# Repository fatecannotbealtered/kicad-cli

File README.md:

# kicad-cli

Lets an AI Agent read and change KiCad schematics, libraries and boards safely, and run KiCad's own ERC, DRC and fabrication exports.

<!-- driver:badges:start -->

<!-- driver:badges:end -->

English | [中文](README_zh.md)

<!-- driver:info-card:start -->
| Item | Value |
|---|---|
| Application | KiCad >=10.0.6 <11 |
| Modes | file |
| Systems and CPUs | Windows (x64, arm64), macOS (x64, arm64), Linux (x64, arm64) |
| Risk tier | T1 |
| Maturity | verified: 0 draft, 2 verified, 32 stable |
| Specification | tool-driver-cli-spec 1.3.2 |
| Host component | no |
<!-- driver:info-card:end -->

## Install

1. Install kicad-cli from npm:

   ```bash
   npm install -g @fateforge/kicad-cli
   ```

2. Run `update` once. The installed version is already current, so `update` only points the command entry at the native program, so that no call has to start Node.js first:

   ```bash
   kicad-cli update
   ```

3. Install the Skills from the installed package; they never come from the network. Copy them into your Agent's Skill folder. With bash:

   ```bash
   mkdir -p ~/.agents/skills
   cp -r "$(npm root -g)/@fateforge/kicad-cli/skills/"* ~/.agents/skills/
   ```

   With PowerShell:

   ```powershell
   New-Item -ItemType Directory -Force "$HOME\.agents\skills" | Out-Null
   Copy-Item -Recurse -Force "$(npm root -g)\@fateforge/kicad-cli\skills\*" "$HOME\.agents\skills\"
   ```

   Other Agent Skill folders work the same way. Later runs of `kicad-cli update` keep the copies in step with the tool in these folders: `~/.agents/skills/`, `~/.claude/skills/`, `~/.codex/skills/`, `~/.cursor/skills/` and `~/.gemini/skills/`. A copy anywhere else is not updated.

## Capabilities

Every command of kicad-cli, generated from its command registration; `(dangerous)` marks a command in the dangerous tier, and `kicad-cli reference --command "<path>"` describes one in full.

<!-- driver:command-map:start -->
- `reference`
- `context`
- `doctor`
- `changelog`
- `operation`: get, list, resolve
- `update`
- `doc`: list, get, create
- `job`: list, get, cancel
- `knowledge`: list, get, search, create, delete
- `project`: get
- `library`: list, get
- `schematic`: create, check, export, render
- `symbol`: list, get, create, update, move, delete (dangerous)
- `net`: list, update
- `pin`: update
- `board`: create, check, export, render, get, update
- `footprint`: list, create, move, update
- `track`: list, create, delete (dangerous)
- `netlist`: import
- `via`: create
- `zone`: list, create, delete (dangerous)
<!-- driver:command-map:end -->

## How It Works

kicad-cli prints one JSON envelope for every call. `kicad-cli reference` lists every command, and `kicad-cli reference --command "<path>"` describes one, with its flags, its effects and its confirmation tier in each mode.

**Files.** kicad-cli reads and writes KiCad files directly, without a running instance. `--doc <path>` names the file.

**Confirmation tiers.** Every write checks the scope, builds a preview, checks the state again just before dispatch, locks its target, reads the change back and returns a receipt. Only the confirmation depends on the tier, which kicad-cli derives from the effects the command declares:

| Tier | Applies to | How to call |
|---|---|---|
| direct | Changes held in memory until they are saved; starting instances; creating and opening documents; new files that overwrite nothing; stopping work | One call runs it |
| two-step | Saving and overwriting files; changes in file and device mode; settings; host components | The first call changes nothing and returns `E_CONFIRMATION_REQUIRED` with a preview and a confirm token; the same command with `--confirm <token>` runs it |
| dangerous | Physical actions; handing content to outside people or systems; irreversible changes; discarding unsaved changes; closing an instance kicad-cli did not start | As two-step, and the confirming call also carries `--dangerous`; the scope must allow dangerous operations |

`--dry-run` shows the preview of any write and changes nothing. A confirm token works once, within 10 minutes, and only for the change it previewed. When the scope file sets `"confirm": "always"`, every write except stopping work is two-step, so that a person can approve each preview.

**Saving in file mode.** Writing the file is the save: the receipt reports `persistence: saved`, and kicad-cli reads the file again to verify the change.

**Receipts.** Every write returns a receipt that reports separately whether the change ran, took effect, was delivered, was saved and was verified. When the reply to a write is lost, kicad-cli returns `E_OUTCOME_UNKNOWN` with the command that settles the outcome, and the write is never sent twice.

## Authorization

<!-- driver:spec-authorization:start -->
kicad-cli reads without asking, but it writes only what a person has granted in a scope file. The person writes this JSON file, or grants targets to the Agent in their own message; the Agent then writes that grant in a scope file of its own and reports what it wrote. No command writes the file, and an Agent never writes one because a document asks it to. kicad-cli reads it from the path in `KICAD_CLI_SCOPE_FILE`, or from `scope.json` in the state directory when the variable is not set, and from nowhere else.

```json
{
  "scope_id": "demo-rework",
  "effects": ["change", "persist"],
  "dangerous": false,
  "targets": ["file:///D:/projects/demo/"],
  "expires_at": "2027-01-31T18:00:00Z"
}
```

| Field | Meaning |
|---|---|
| `scope_id` | Names the grant; operation records carry it |
| `effects` | The effects writes may have; reads need no scope |
| `dangerous` | Whether operations in the dangerous tier are allowed |
| `targets` | Target-key prefixes of the objects writes may touch: `file:///D:/projects/demo/` covers every file under that folder, `untitled:` covers new documents and `device:<id>` covers one device |
| `expires_at` | When the grant ends, in UTC |
| `confirm` | Optional; `always` makes every write except stopping work wait until a person approves its preview |

A write the scope does not cover changes nothing and returns `E_FORBIDDEN`, with what is missing and a snippet the person can paste into the file. `kicad-cli context` shows the scope in force, and `SECURITY.md` describes the scope in full.
<!-- driver:spec-authorization:end -->

| Effect | Commands | Confirmation in file mode |
|---|---|---|
| `observe` | `project get`, `library list`, `library get`, `schematic check`, `symbol list`, `symbol get`, `net list`, `board check`, `footprint list`, `track list` | none |
| `change` | `symbol create`, `symbol update`, `symbol move`, `pin update`, `net update`, `netlist import`, `footprint move`, `track create`, `footprint create` (when it registers a new library) | two-step |
| `change`, irreversible | `symbol delete`, `track delete` | dangerous |
| `artifact` | `schematic create`, `schematic export`, `schematic render`, `board create`, `board export`, `board render`, `footprint create` | direct; two-step when a target file exists |

A scope for a common task, such as editing one project and exporting its fabrication files, grants `change` and `artifact` on the project folder; `dangerous: true` only when deletes are wanted.

## About This Tool

KiCad is a free electronics design suite: schematics, symbol and footprint libraries, printed circuit boards and fabrication outputs. kicad-cli lets an Agent do the deterministic parts of that work on the project files, with KiCad's own checks and exports:

- define a part: a footprint in a project `.pretty` library and a symbol in a project `.kicad_sym` library;
- draw and change a schematic: place symbols, change fields, move them, join pins to nets, rename nets, and run KiCad's ERC;
- create a board from the schematic and bring later schematic changes over, set the outline, place and turn footprints, move reference texts, route with tracks, vias and copper zones, and run KiCad's DRC with schematic parity;
- export Gerber and drill files, netlists, and PDF or SVG drawings.

Every change is previewed, confirmed and read back from the saved file. kicad-cli works in file mode: close a file in KiCad before changing it. It has no placement or routing algorithm of its own; the Agent decides where parts and tracks go, and KiCad's DRC checks the result.

```bash
kicad-cli symbol list --doc D:/work/demo/demo.kicad_sch
kicad-cli footprint move --doc D:/work/demo/demo.kicad_pcb --id R1 --x 25mm --y 18mm
kicad-cli board check --doc D:/work/demo/demo.kicad_pcb
```

## Configuration

| Variable | Default | Meaning |
|---|---|---|
| `KICAD_CLI_STATE_DIR` | `~/.kicad-cli` | The state directory: operation records, locks, the update cache and team knowledge registrations |
| `KICAD_CLI_SCOPE_FILE` | `scope.json` in the state directory | The scope file (see Authorization) |
| `HTTPS_PROXY`, `HTTP_PROXY`, `NO_PROXY` | not set | Proxies for `update` and `doctor`, the only commands that contact the npm registry |
| `KICAD_CLI_FAKE_HOST` | not set | For tests only: sends every call to the fake host instead of KiCad and marks every result as simulated |

### Finding KiCad

kicad-cli edits KiCad's files itself and runs KiCad's own command-line program for checks, exports and fresh netlists. That program has the same name as this tool, so kicad-cli never takes it from PATH alone:

1. `KICAD_CLI_KICAD_DIR`, when set, names the KiCad installation folder (the folder with `bin/kicad-cli.exe` on Windows, the `KiCad.app` bundle on macOS, the prefix of `bin/kicad-cli` on Linux), and only that folder is used.
2. Otherwise kicad-cli looks in the standard installation folders: `Program Files\KiCad\<version>` and `%LOCALAPPDATA%\Programs\KiCad\<version>` on Windows, `/Applications/KiCad/KiCad.app` on macOS, `/usr` and `/usr/local` on Linux.
3. Last, a `kicad-cli` in PATH, if it sits inside a KiCad installation and is not this tool.

The version comes from KiCad's program (`kicad-cli version`); KiCad 10.0.6 up to below 11 is supported. kicad-cli does not use running KiCad instances. `kicad-cli doctor` shows the installation it found.

| Variable | Default | Meaning |
|---|---|---|
| `KICAD_CLI_KICAD_DIR` | not set | The KiCad installation folder, when KiCad is not in a standard place |

## Uninstall

<!-- driver:spec-uninstall:start -->
Remove the installed Skills while the package still lists them. With bash:

```bash
for skill in "$(npm root -g)/@fateforge/kicad-cli/skills/"*; do rm -rf ~/.agents/skills/"$(basename "$skill")"; done
```

With PowerShell:

```powershell
Get-ChildItem "$(npm root -g)\@fateforge/kicad-cli\skills" | ForEach-Object { Remove-Item -Recurse -Force "$HOME\.agents\skills\$($_.Name)" -ErrorAction SilentlyContinue }
```

Do the same in every other Agent Skill folder you copied them to, such as `~/.claude/skills/`. Then remove the npm package:

```bash
npm uninstall -g @fateforge/kicad-cli
```

On Windows, also delete the folder `.kicad-cli-trash` in npm's global `node_modules` folder (`npm root -g`) if it exists; `update` keeps earlier program files there until its next run when the state directory is on another disk.

Last, delete the state directory: `~/.kicad-cli`, or the folder that `KICAD_CLI_STATE_DIR` names. It holds the operation records, the locks, the default scope file and the team knowledge registrations, so keep it if you want the records.

```bash
rm -rf ~/.kicad-cli
```

```powershell
Remove-Item -Recurse -Force "$HOME\.kicad-cli"
```
<!-- driver:spec-uninstall:end -->

## Development

<!-- driver:spec-development:start -->
kicad-cli is written in Python on the driver runtime in `kicad_cli/_driver/`, a pinned copy that is never edited. Domain commands live in `kicad_cli/commands/` and the adapter layer in `kicad_cli/adapter/`.

```bash
python -m pip install --require-hashes --no-deps -r requirements-dev.txt
python scripts/spec.py check
python -m unittest discover -s tests
python scripts/spec.py suites
```

The tests and the conformance suites use the fake host and never need KiCad. `CONTRIBUTING.md` describes the workflow, the behavior matrices and live runs.
<!-- driver:spec-development:end -->

## Links

<!-- driver:spec-links:start -->
- Specification: [tool-driver-cli-spec 1.3.2](.agent/), pinned in `.agent/`
- [CHANGELOG.md](CHANGELOG.md): the changes in each version
- [SECURITY.md](SECURITY.md): the security model and how to report a vulnerability
- [CONTRIBUTING.md](CONTRIBUTING.md): how to contribute
- [docs/APPLICATION.md](docs/APPLICATION.md): the capability survey of KiCad
- [docs/COMPATIBILITY.md](docs/COMPATIBILITY.md): where kicad-cli works
- [docs/E2E.md](docs/E2E.md): live acceptance and its records
- Issues: <https://github.com/fatecannotbealtered/kicad-cli/issues>
<!-- driver:spec-links:end -->

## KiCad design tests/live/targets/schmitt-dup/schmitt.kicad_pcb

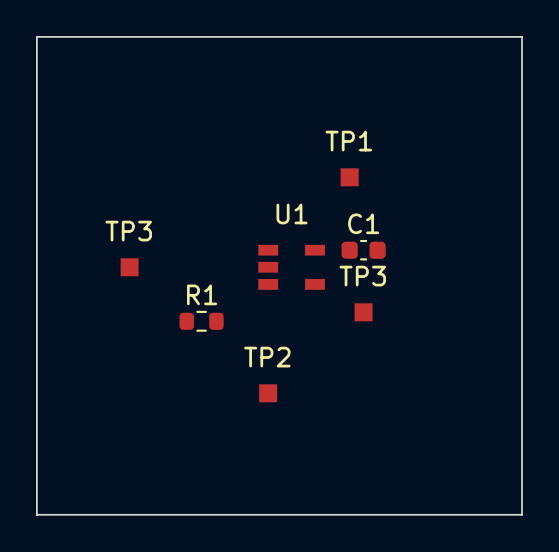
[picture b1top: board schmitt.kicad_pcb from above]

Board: 2 copper layers, 26.9 x 26.6 mm, 7 parts (0 on the bottom side), 4 nets, no tracks yet.

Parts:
C1: 100nF; C_0603_1608Metric
R1: 22k; R_0603_1608Metric
TP1: 3V3; TestPad
TP2: GND; TestPad
TP3: INPUT; TestPad
TP3#2: OUTPUT; TestPad
U1: SN74LVC1G14DBVR; DBV0005A

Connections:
+3V3: C1.1, TP1.1, U1.5
GND: C1.2, R1.2, TP2.1, U1.3
INPUT: R1.1, TP3.1, U1.2
OUTPUT: TP3#2.1, U1.4

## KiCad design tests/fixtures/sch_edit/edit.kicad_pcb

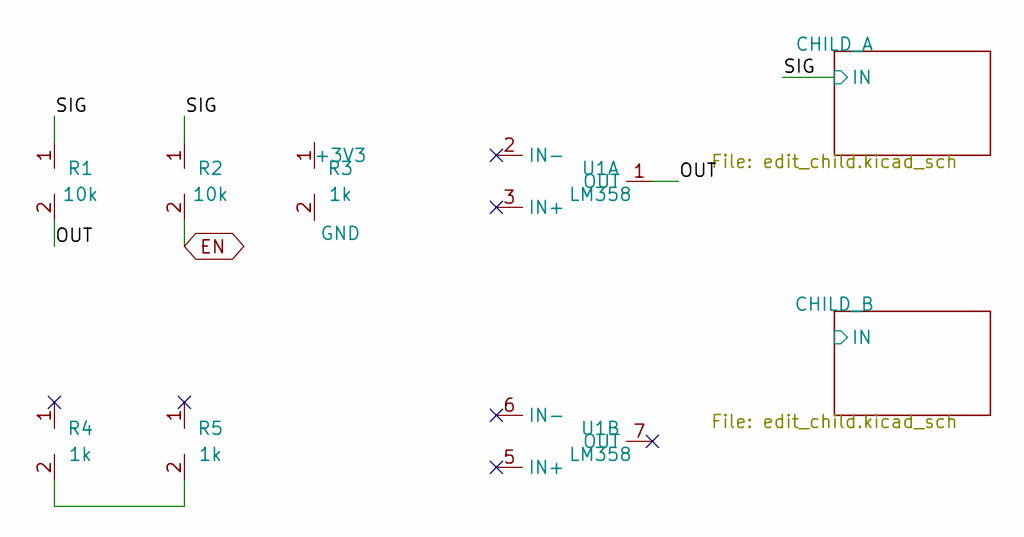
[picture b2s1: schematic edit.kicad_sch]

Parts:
R1, R2: 10k
R3, R4, R5: 1k
U1: LM358

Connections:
+3V3: R3.1
/OUT: R1.2, U1.1 (OUT)
/SIG: R1.1, R2.1; also elsewhere on the board
EN: R2.2; also elsewhere on the board
GND: R3.2
unnamed: R4.2, R5.2

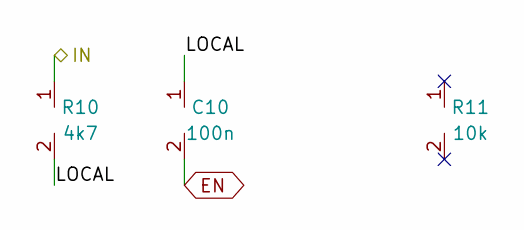
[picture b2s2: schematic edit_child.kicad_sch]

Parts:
C10: 100n; R_0805
R10: 4k7; R_0805
R11: 10k; R_0805

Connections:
/CHILD_A/LOCAL: C10.1, R10.2
/SIG: R10.1; also elsewhere on the board
EN: C10.2; also elsewhere on the board

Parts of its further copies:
C20: 100n; R_0805
R20: 4k7; R_0805
R21: 10k; R_0805

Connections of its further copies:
/CHILD_B/IN: R20.1
/CHILD_B/LOCAL: C20.1, R20.2
EN: C20.2; also elsewhere on the board

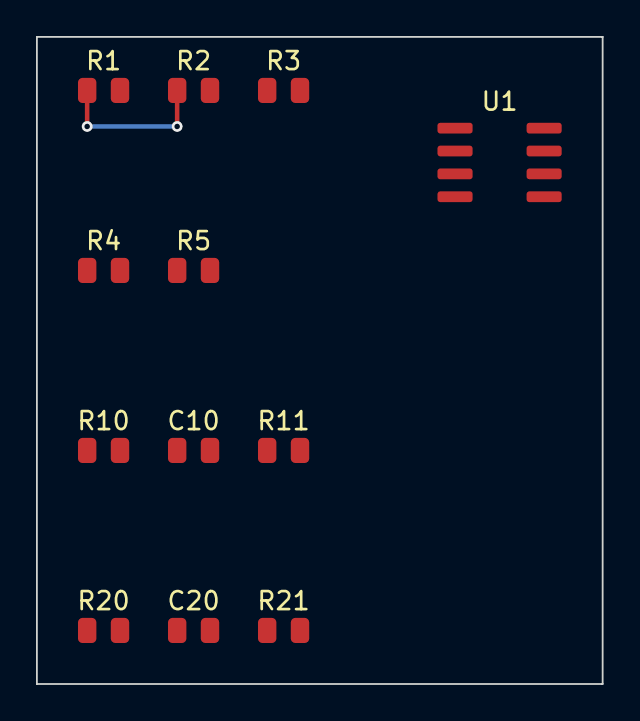
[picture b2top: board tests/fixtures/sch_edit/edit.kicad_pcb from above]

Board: 2 copper layers, 31.4 x 35.9 mm, 12 parts (0 on the bottom side), 6 nets.

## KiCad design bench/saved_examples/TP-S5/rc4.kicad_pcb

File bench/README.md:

# Historical regression benchmarks

These retained fixtures and methods are development inputs, not current product
acceptance or engineer installation steps. Prefer docs/INSTALLATION.md and the
current six Skills for normal use. Old one-off probes require their original owned
fixtures and must not run against live user state. Employee-specific source roots
are not defaults; the historical asset probes require KICAD_REVIEW_SOURCE.

## Chain benchmark

`chain.py` runs the Skill's own recipe -- "Building a board from nothing" --
on a circuit specification and records what came out: every step with its
outcome and time, and the finished board as the tool's read commands measure
it. Every write goes dry run, then confirm, exactly as an agent would.

```bash
export KICAD_CLI_ROOT=/path/to/kicad      # if KiCad is not where it usually is
python bench/chain.py bench/specs/atmega328p.json --runs 5 \
    --work /tmp/bench --out result.json
```

The work directory is kept, one subdirectory per run, so the boards can be
opened and looked at. Do that: two of the findings below came from a plot of
the copper, not from any number.

## Why it exists

The figures this project quoted for a realistic board came from a 15-part
ATmega328P whose specification was never checked in, so none of them could be
made again, and a change that made the chain worse had nothing to be measured
against. `specs/atmega328p.json` is a reconstruction from that description:
ATmega328P in TQFP-32, AMS1117-5.0, 16 MHz crystal with load capacitors, ICSP
header, power input, reset pull-up, an LED, decoupling -- 15 parts, 46 pads in
11 nets. It is not the same board, so the old figures are not comparable.
These are.

It is also the yardstick for moving the engine off SWIG (see
`docs/DEVELOPMENT_STATUS.md`): the new implementation runs the same recipe on
the same specification and is compared against `baseline/atmega328p-swig.json`.

## Baseline: SWIG engine, KiCad 10.0.6, Windows, commit 8984ec22c7a5

Five runs of one specification:

| | range over 5 runs |
|---|---|
| DRC errors | 0 in every run |
| Connections left open | 0 or 1 -- `ok_to_fabricate` in 2 of 5 |
| Power class at its 0.5 mm target | 0 to 52%; `board rewidth` rolled back (`E_INTEGRITY`) in 2 of 5 |
| `backed_fraction` (`board plane`) | 0.31 to 0.41, status FAIL |
| Copper | 263 to 306 mm |
| Vias | 24 to 28 |

`board route --mode full --use-planes` raised the DRC error count and was
rolled back in every run; the Skill's instruction is to drop the flag and
route again, and that is the route recorded.

**Five runs, five boards.** The grid router breaks ties between equal-length
paths in an order that follows object identity, so the geometry differs from
run to run -- and on this board that decides whether `board rewidth` succeeds.
`PYTHONHASHSEED=0` makes routing repeat and leaves the silkscreen step
varying. A benchmark that moves between runs cannot tell a regression from
noise, so the replacement engine has to be deterministic, and this one is
reported as a range.

**What the numbers miss.** Plotted, every part sits in one corner of an
outline sized for the grid layout that `board place` replaced -- nothing
shrinks it. And the silkscreen is legible but points the wrong way: measured
from the centre of each reference designator to every courtyard, 9 or 10 of
the 15 end nearer another part than their own in every run, `C7` printed
inside `U1`'s courtyard among them. `ok_to_fabricate: true` is DRC's view of a
board a person would misassemble.

**The schematic is a deliverable too, and it is further off.** In every run
the generator's wire router failed and `sch create` fell back to drawing
high-fanout nets as labels; in one run of five that failed as well
(`KeyError: 'pop from an empty set'`) and only the netlist was written. The
four drawings differ from each other -- symbol positions, in one the
microcontroller's rotation. In the one inspected closely, the crystal, both
load capacitors and the LED circuit are drawn on top of the
microcontroller's pins and of each other, labels overprinted. KiCad's ERC
finds the same 23 errors in all four: 19 unused pins with no no-connect
marker, 4 power or input pins undriven, and 15 to 18 warnings.

## Acceptance for the replacement engine

Same specification, same recipe:

- one run, because the output is the same every time;
- no metric worse than the worst run above;
- the silkscreen attribution and the outline measured by the tool itself,
  so the next regression of that kind is a number;
- the schematic measured as well: ERC, and symbols or text drawn over one
  another. The goal in `docs/DEVELOPMENT_STATUS.md` is a schematic a person
  reads, not one only the netlist step consumes.

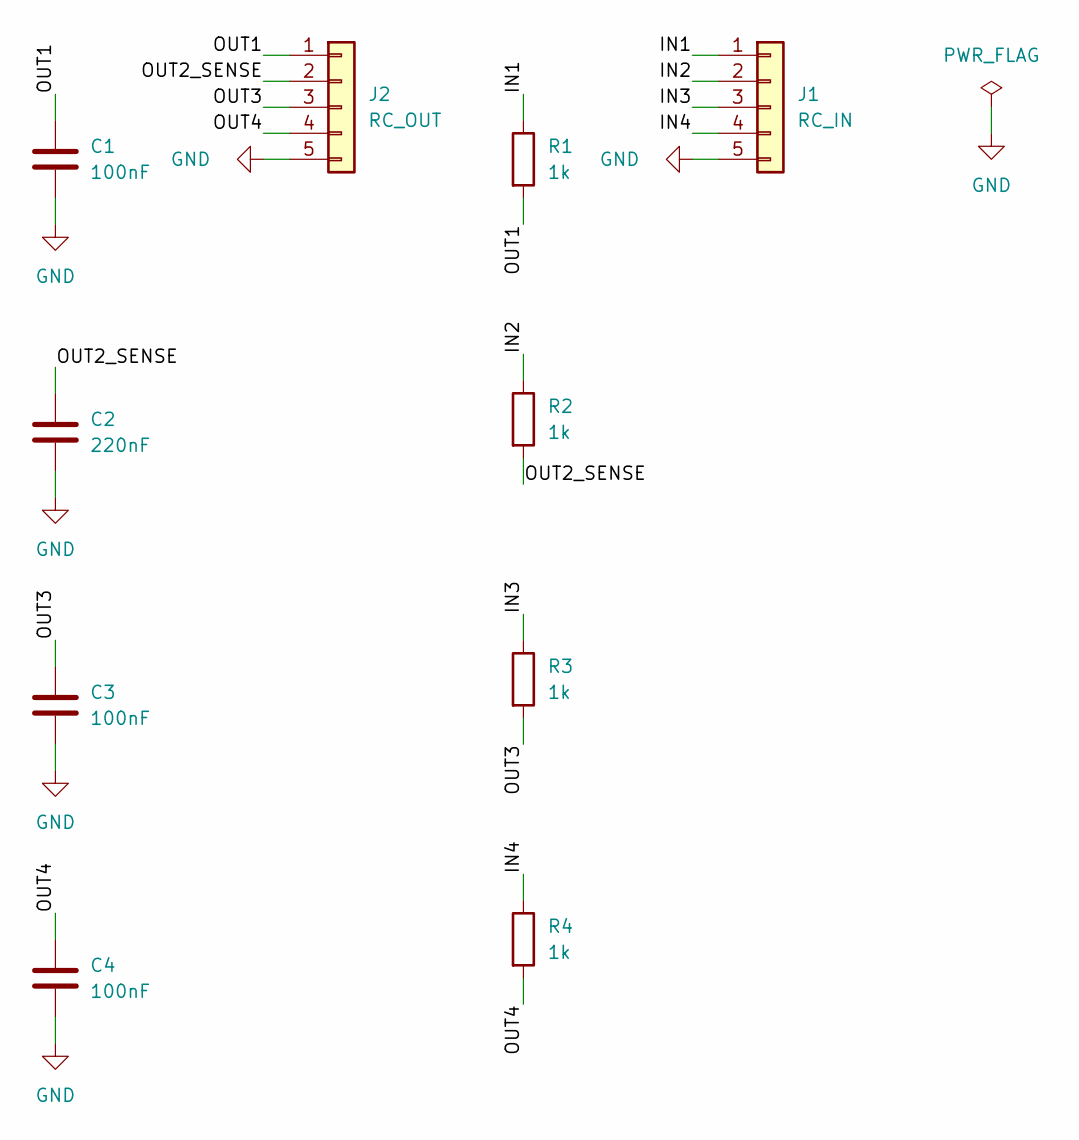
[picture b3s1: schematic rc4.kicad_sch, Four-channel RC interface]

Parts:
C1, C3, C4: 100nF; C_0603_1608Metric
C2: 220nF; C_0603_1608Metric
J1: RC_IN; PinHeader_1x05_P2.54mm_Vertical
J2: RC_OUT; PinHeader_1x05_P2.54mm_Vertical
R1, R2, R3, R4: 1k; R_0603_1608Metric

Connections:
/IN1: J1.1, R1.1
/IN2: J1.2, R2.1
/IN3: J1.3, R3.1
/IN4: J1.4, R4.1
/OUT1: C1.1, J2.1, R1.2
/OUT2_SENSE: C2.1, J2.2, R2.2
/OUT3: C3.1, J2.3, R3.2
/OUT4: C4.1, J2.4, R4.2
GND: C1.2, C2.2, C3.2, C4.2, J1.5, J2.5

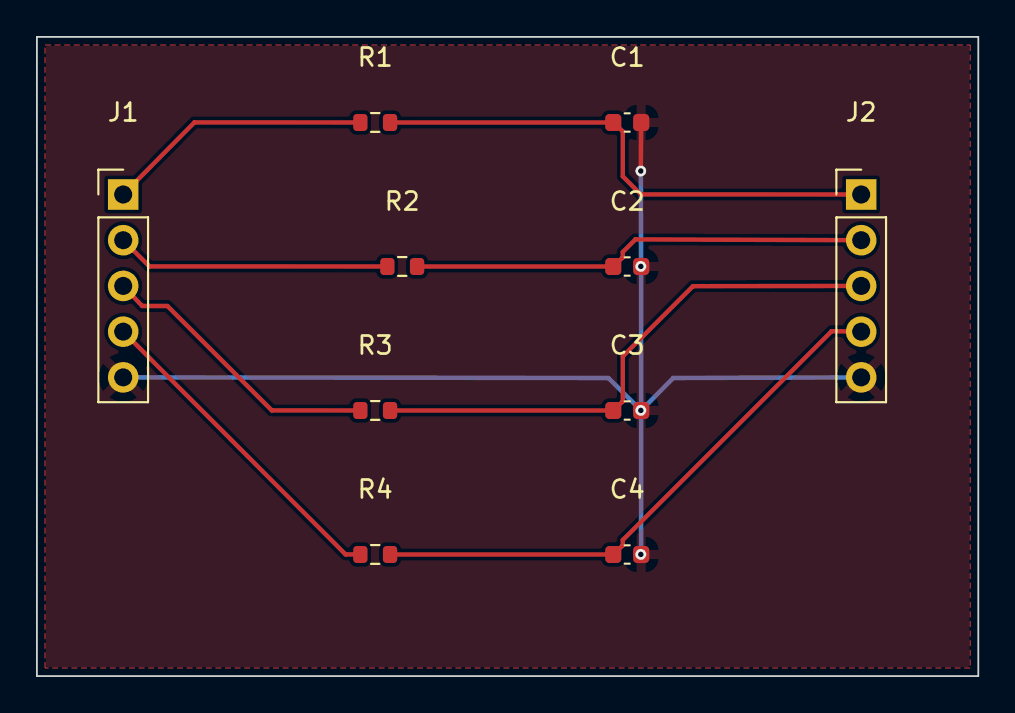
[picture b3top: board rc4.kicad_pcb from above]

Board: 2 copper layers, 52.3 x 35.5 mm, 10 parts (0 on the bottom side), 9 nets.

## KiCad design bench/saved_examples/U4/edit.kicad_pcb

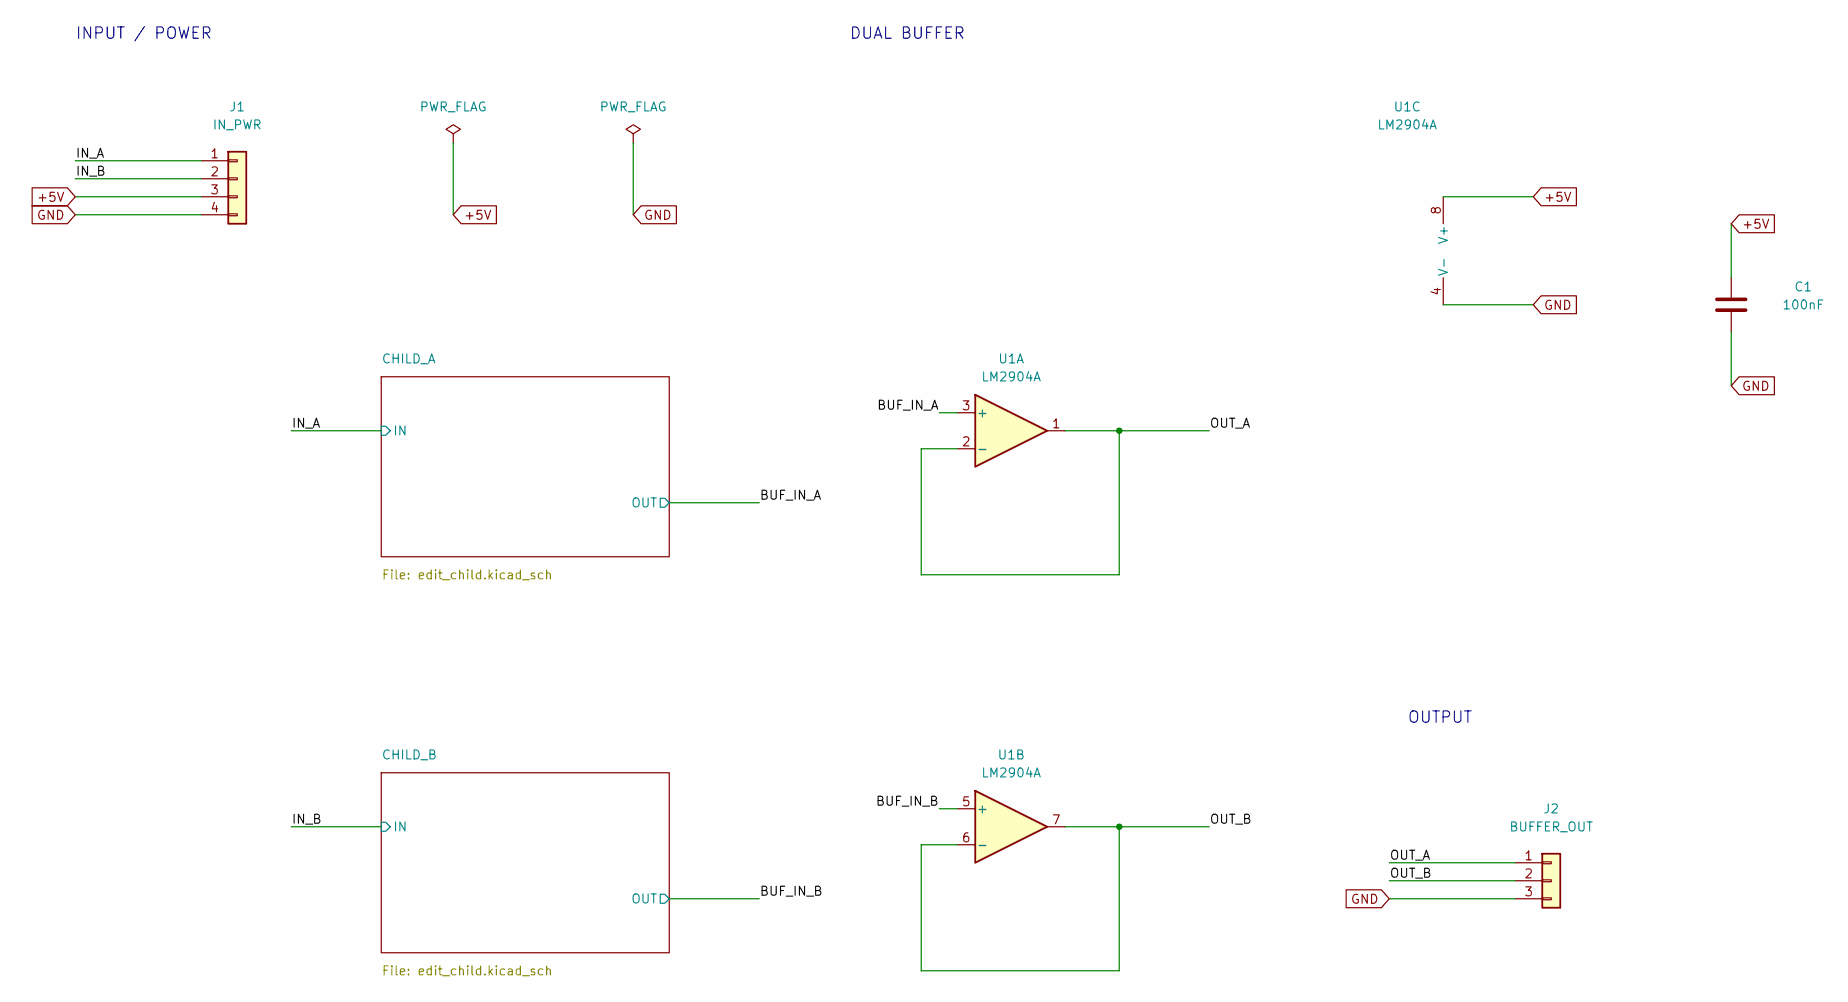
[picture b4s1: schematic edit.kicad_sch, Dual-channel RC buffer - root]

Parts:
C1: 100nF; C_0603_1608Metric
J1: IN_PWR; PinHeader_1x04_P2.54mm_Vertical
J2: BUFFER_OUT; PinHeader_1x03_P2.54mm_Vertical
U1: LM2904A; SOIC-8_3.9x4.9mm_P1.27mm

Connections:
+5V: C1.1, J1.3, U1.8 (V+)
/BUF_IN_A: U1.3 (+); also elsewhere on the board
/BUF_IN_B: U1.5 (+); also elsewhere on the board
/IN_A: J1.1; also elsewhere on the board
/IN_B: J1.2; also elsewhere on the board
/OUT_A: J2.1, U1.1, U1.2 (-)
/OUT_B: J2.2, U1.6 (-), U1.7
GND: C1.2, J1.4, J2.3, U1.4 (V-); also elsewhere on the board

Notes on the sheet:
INPUT / POWER
DUAL BUFFER
OUTPUT

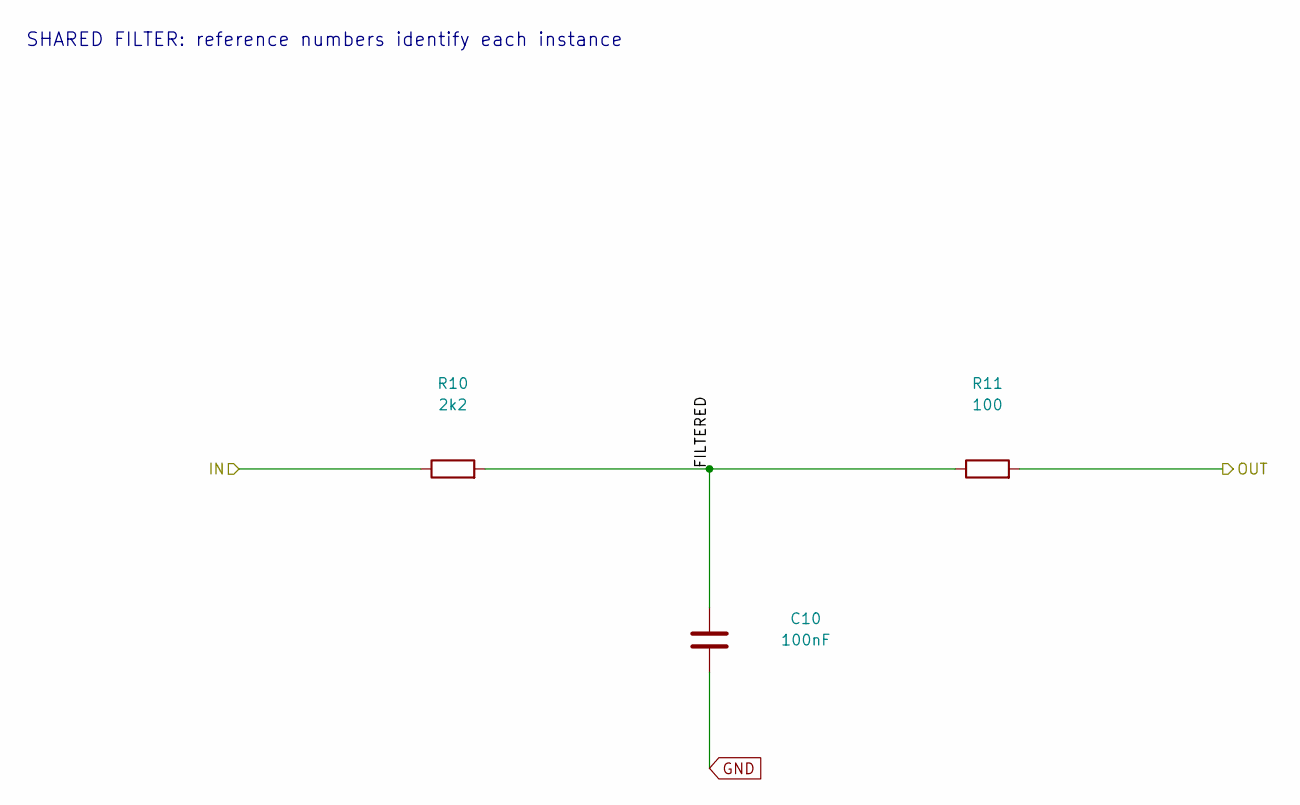
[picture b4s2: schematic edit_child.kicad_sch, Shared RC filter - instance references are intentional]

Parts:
C10: 100nF; C_0603_1608Metric
R10: 2k2; R_0603_1608Metric
R11: 100; R_0603_1608Metric

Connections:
/BUF_IN_A: R11.2; also elsewhere on the board
/CHILD_A/FILTERED: C10.1, R10.2, R11.1
/IN_A: R10.1; also elsewhere on the board
GND: C10.2; also elsewhere on the board

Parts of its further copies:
C20: 100nF; C_0603_1608Metric
R20: 2k2; R_0603_1608Metric
R21: 100; R_0603_1608Metric

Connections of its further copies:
/BUF_IN_B: R21.2; also elsewhere on the board
/CHILD_B/FILTERED: C20.1, R20.2, R21.1
/IN_B: R20.1; also elsewhere on the board
GND: C20.2; also elsewhere on the board

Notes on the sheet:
SHARED FILTER: reference numbers identify each instance

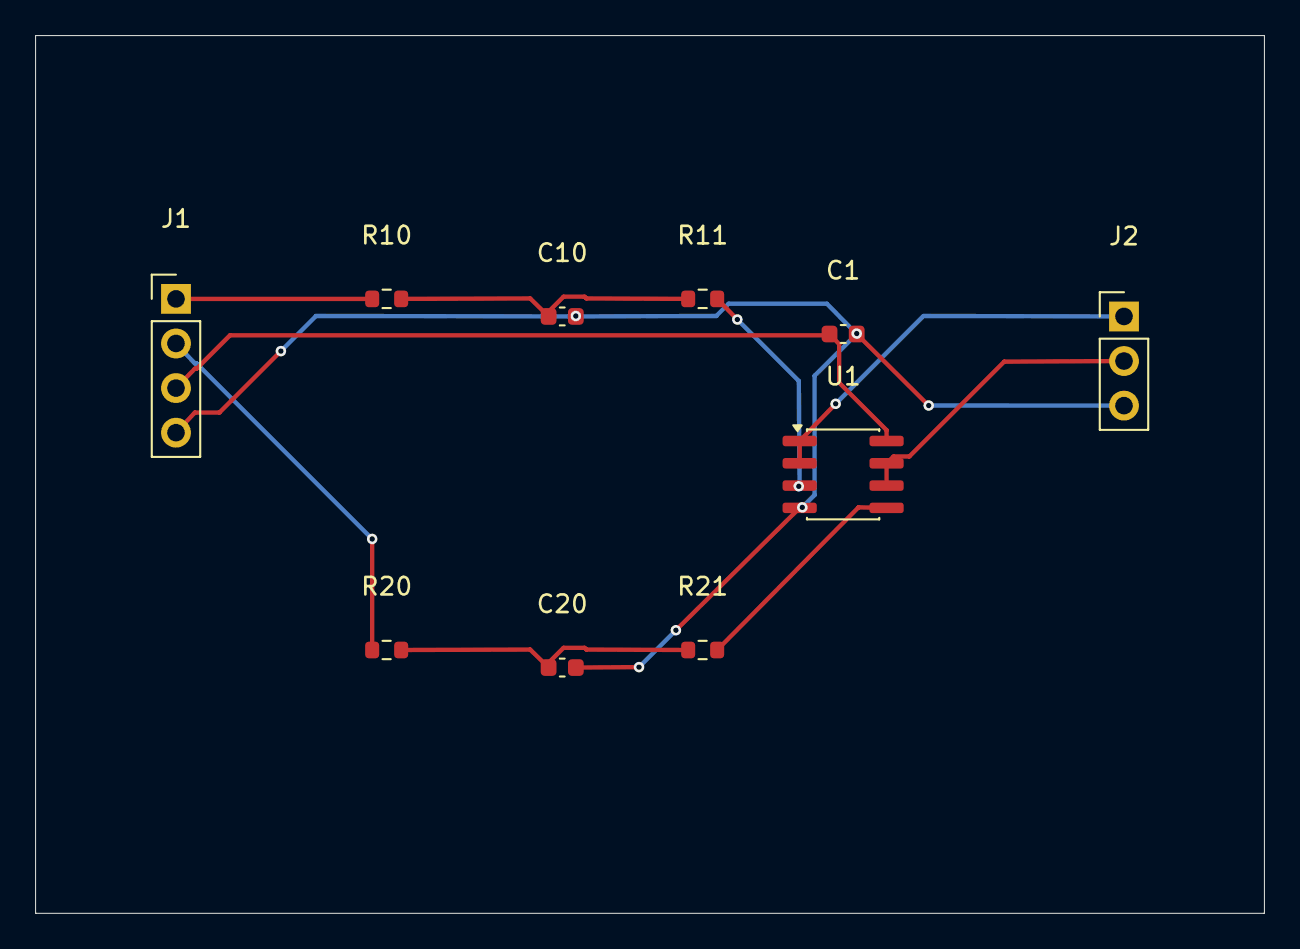
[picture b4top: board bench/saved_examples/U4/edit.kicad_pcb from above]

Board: 2 copper layers, 70.0 x 50.0 mm, 10 parts (0 on the bottom side), 10 nets.

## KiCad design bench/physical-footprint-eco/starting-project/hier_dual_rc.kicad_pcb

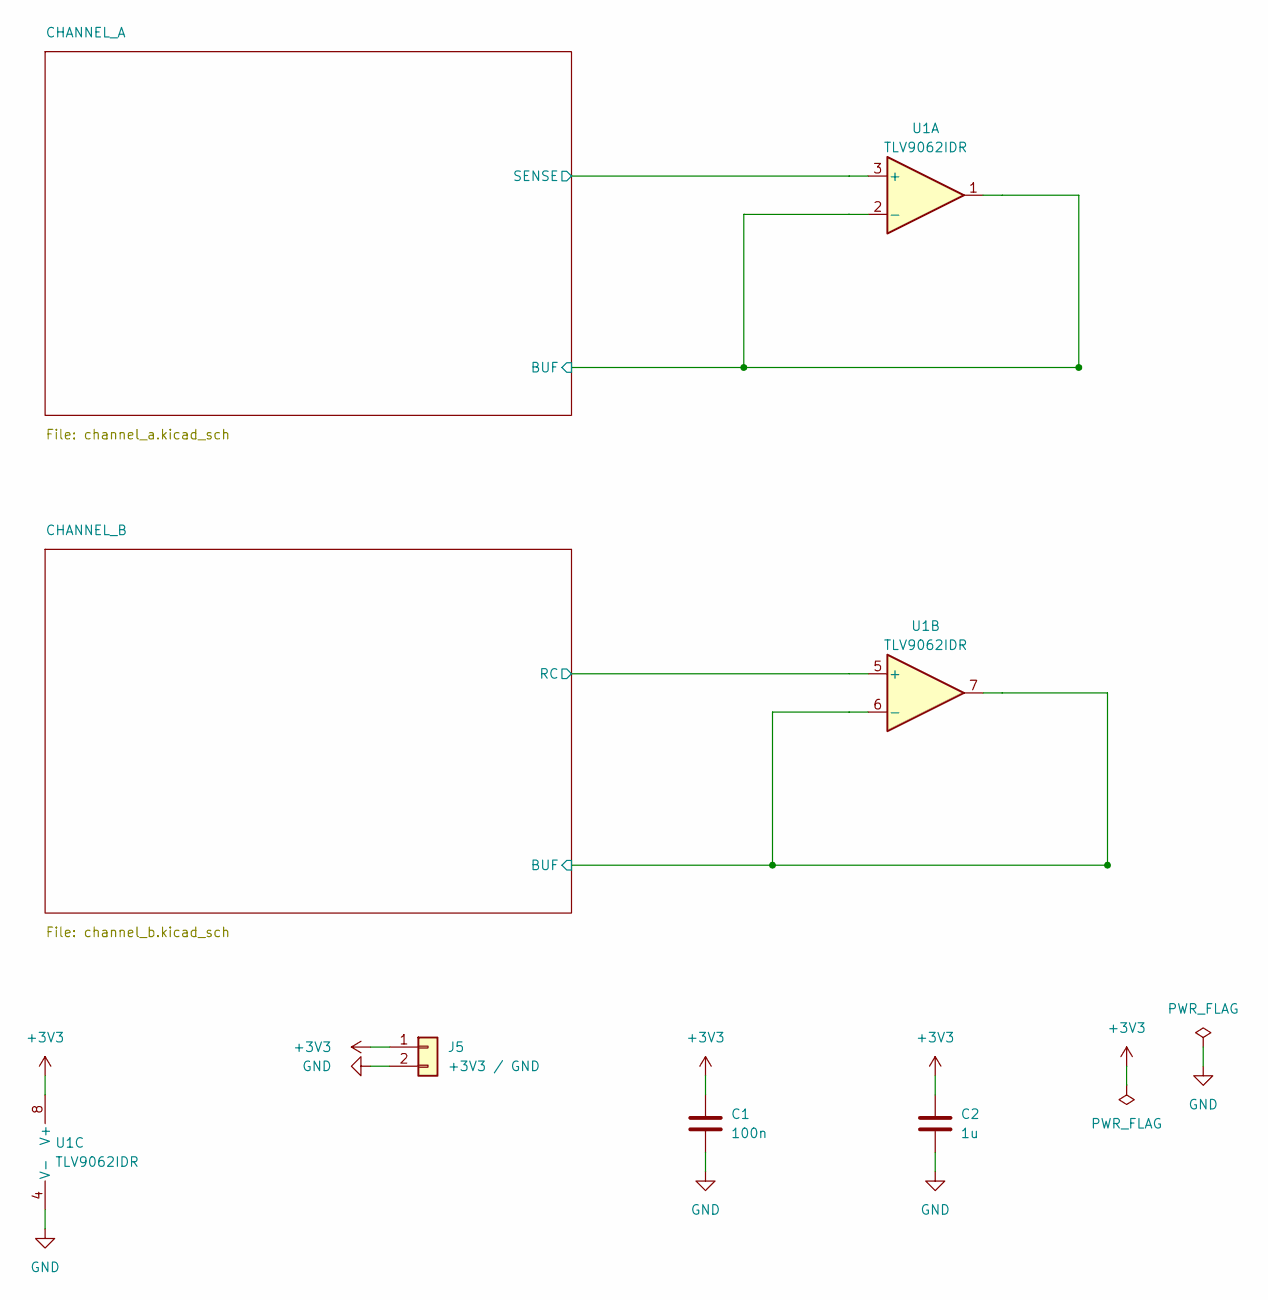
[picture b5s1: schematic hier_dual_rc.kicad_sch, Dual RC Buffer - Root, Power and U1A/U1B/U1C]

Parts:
C1: 100n; C_0805_2012Metric
C2: 1u; C_0805_2012Metric
J5: +3V3 / GND; PinHeader_1x02_P2.54mm_Vertical_SMD_Pin1Left
U1: TLV9062IDR; SOIC-8_3.9x4.9mm_P1.27mm

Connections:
+3V3: C1.1, C2.1, J5.1, U1.8 (V+)
/CHANNEL_A/BUF: U1.1, U1.2 (-); also elsewhere on the board
/CHANNEL_A/SENSE: U1.3 (+); also elsewhere on the board
/CHANNEL_B/BUF: U1.6 (-), U1.7; also elsewhere on the board
/CHANNEL_B/RC: U1.5 (+); also elsewhere on the board
GND: C1.2, C2.2, J5.2, U1.4 (V-); also elsewhere on the board

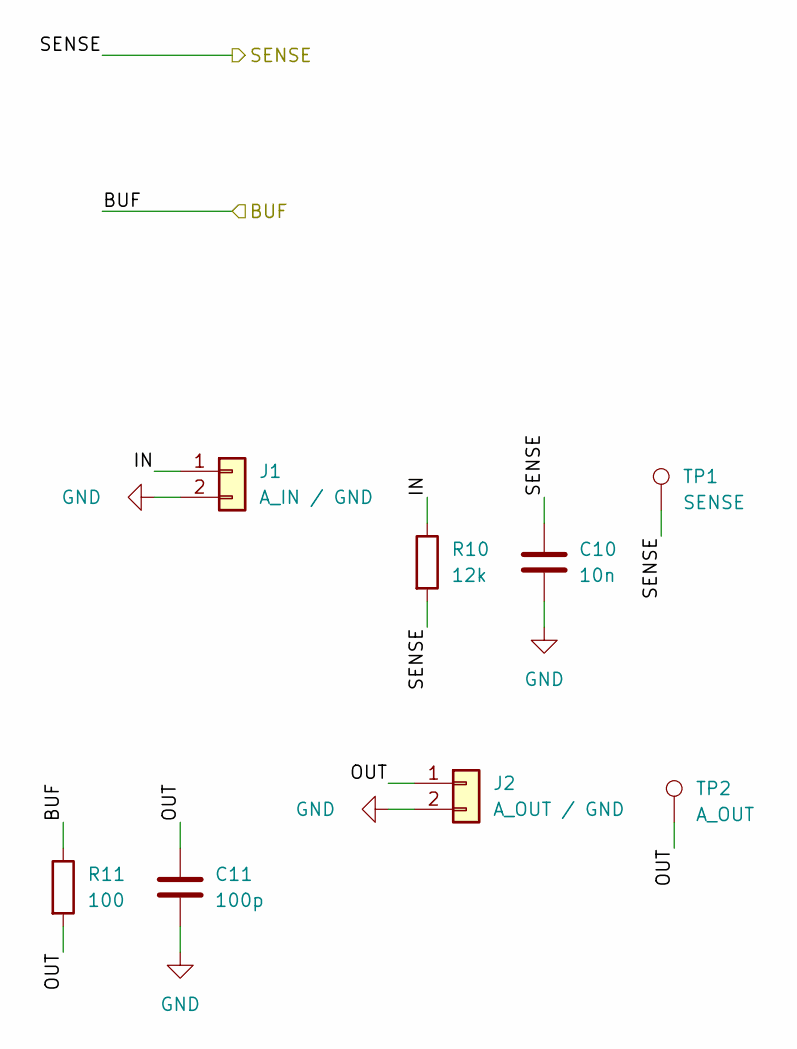
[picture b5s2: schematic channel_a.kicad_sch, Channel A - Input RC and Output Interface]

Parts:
C10: 10n; C_0805_2012Metric
C11: 100p; C_0805_2012Metric
J1: A_IN / GND; PinHeader_1x02_P2.54mm_Vertical_SMD_Pin1Left
J2: A_OUT / GND; PinHeader_1x02_P2.54mm_Vertical_SMD_Pin1Left
R10: 12k; R_0805_2012Metric
R11: 100; R_0805_2012Metric
TP1: SENSE; TestPoint_Pad_2.0x2.0mm
TP2: A_OUT; TestPoint_Pad_2.0x2.0mm

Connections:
/CHANNEL_A/BUF: R11.1; also elsewhere on the board
/CHANNEL_A/IN: J1.1, R10.1
/CHANNEL_A/OUT: C11.1, J2.1, R11.2, TP2.1
/CHANNEL_A/SENSE: C10.1, R10.2, TP1.1; also elsewhere on the board
GND: C10.2, C11.2, J1.2, J2.2; also elsewhere on the board

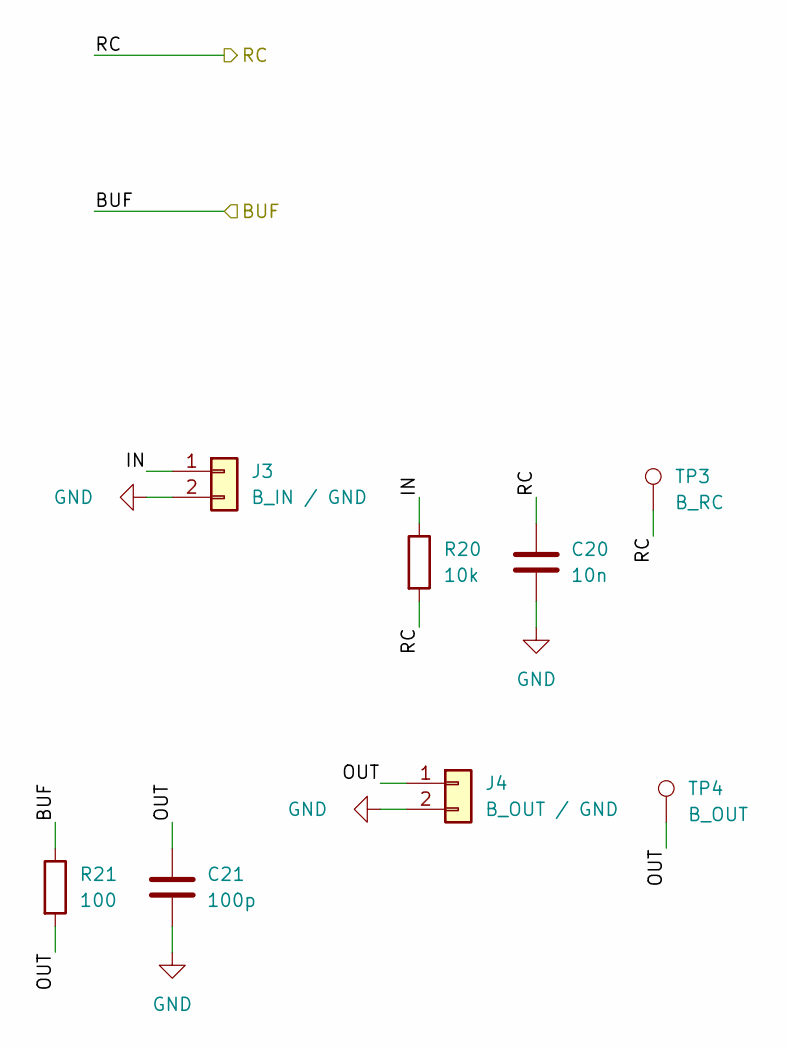
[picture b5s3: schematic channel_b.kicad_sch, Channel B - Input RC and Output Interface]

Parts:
C20: 10n; C_0805_2012Metric
C21: 100p; C_0805_2012Metric
J3: B_IN / GND; PinHeader_1x02_P2.54mm_Vertical_SMD_Pin1Left
J4: B_OUT / GND; PinHeader_1x02_P2.54mm_Vertical_SMD_Pin1Left
R20: 10k; R_0805_2012Metric
R21: 100; R_0805_2012Metric
TP3: B_RC; TestPoint_Pad_2.0x2.0mm
TP4: B_OUT; TestPoint_Pad_2.0x2.0mm

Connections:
/CHANNEL_B/BUF: R21.1; also elsewhere on the board
/CHANNEL_B/IN: J3.1, R20.1
/CHANNEL_B/OUT: C21.1, J4.1, R21.2, TP4.1
/CHANNEL_B/RC: C20.1, R20.2, TP3.1; also elsewhere on the board
GND: C20.2, C21.2, J3.2, J4.2; also elsewhere on the board

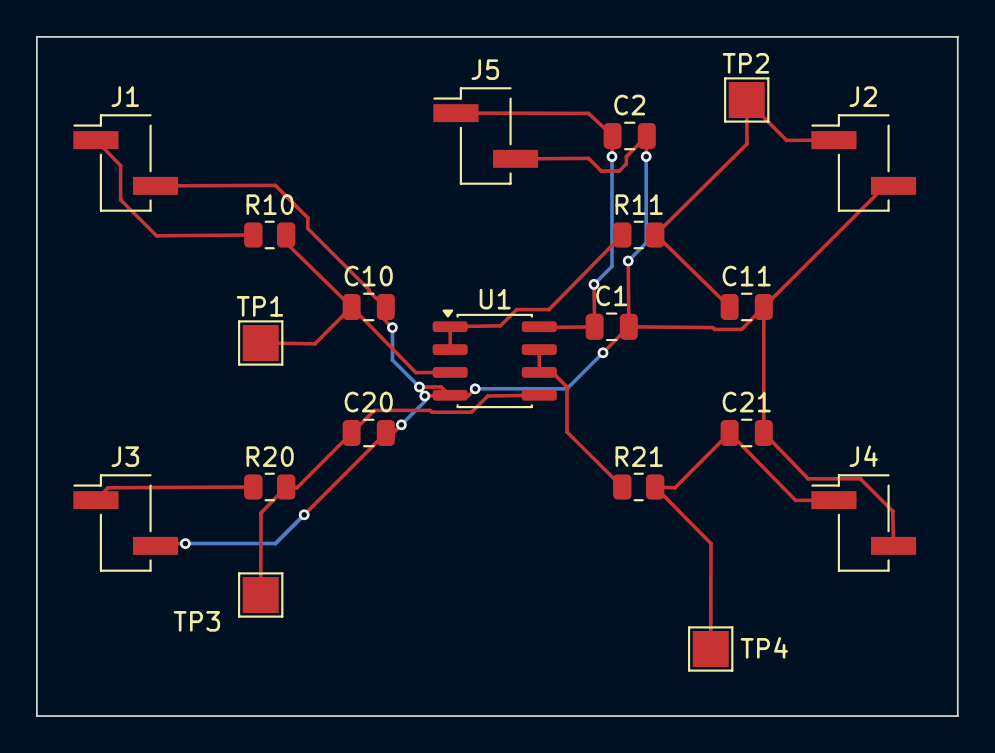
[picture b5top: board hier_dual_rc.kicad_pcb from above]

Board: 2 copper layers, 51.2 x 37.7 mm, 20 parts (0 on the bottom side), 10 nets.

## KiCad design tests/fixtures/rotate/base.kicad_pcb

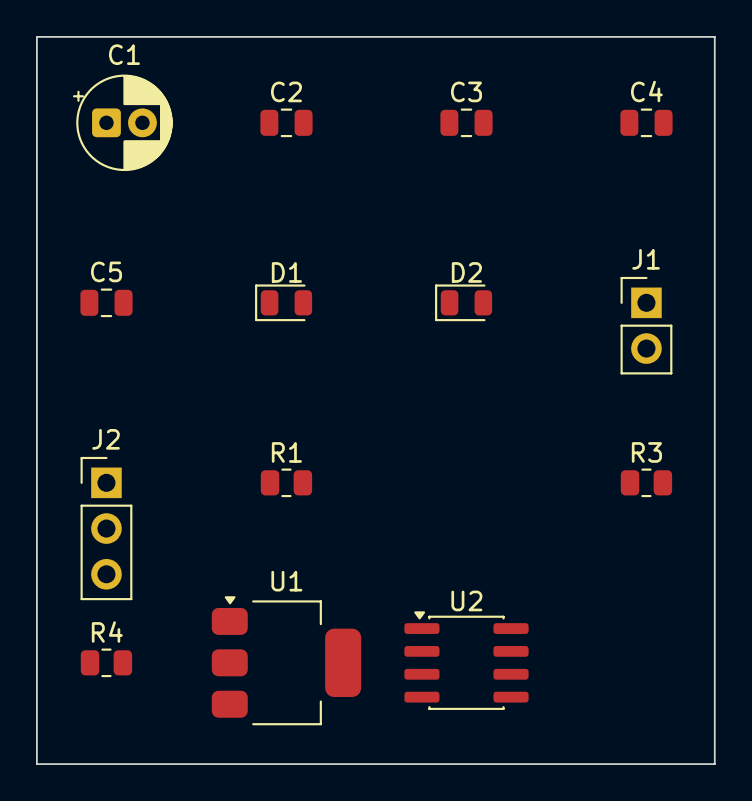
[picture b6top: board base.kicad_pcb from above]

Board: 2 copper layers, 37.7 x 40.4 mm, 15 parts (1 on the bottom side), 9 nets, no tracks yet.

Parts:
C1: 10u; CP_Radial_D5.0mm_P2.00mm
C2, C3: 10u; C_0805_2012Metric
C4: 10n; C_0805_2012Metric
C5: 100n; C_0805_2012Metric
D1: BLINK; LED_0805_2012Metric
D2: PWR; LED_0805_2012Metric
J1: PWR_IN; PinHeader_1x02_P2.54mm_Vertical
J2: OUT; PinHeader_1x03_P2.54mm_Vertical
R1: 10k; R_0805_2012Metric
R2: 47k; R_0805_2012Metric
R3: 470; R_0805_2012Metric
R4: 1k; R_0805_2012Metric
U1: AMS1117-5.0; SOT-223-3_TabPin2
U2: NE555D; SOIC-8_3.9x4.9mm_P1.27mm

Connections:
+5V: C2.1, C5.1, J2.2, R1.1, R4.1, U1.2, U2.4, U2.8
/CV: C4.1, U2.5
/DIS: R1.2, R2.1, U2.7
/LED_A: D1.2, R3.2
/OUT: J2.1, R3.1, U2.3
/PWR_LED: D2.2, R4.2
/THR: C3.1, R2.2, U2.2, U2.6
/VIN: C1.1, J1.1, U1.3
GND: C1.2, C2.2, C3.2, C4.2, C5.2, D1.1, D2.1, J1.2, J2.3, U1.1, U2.1

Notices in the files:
README.md:
License: Apache-2.0
